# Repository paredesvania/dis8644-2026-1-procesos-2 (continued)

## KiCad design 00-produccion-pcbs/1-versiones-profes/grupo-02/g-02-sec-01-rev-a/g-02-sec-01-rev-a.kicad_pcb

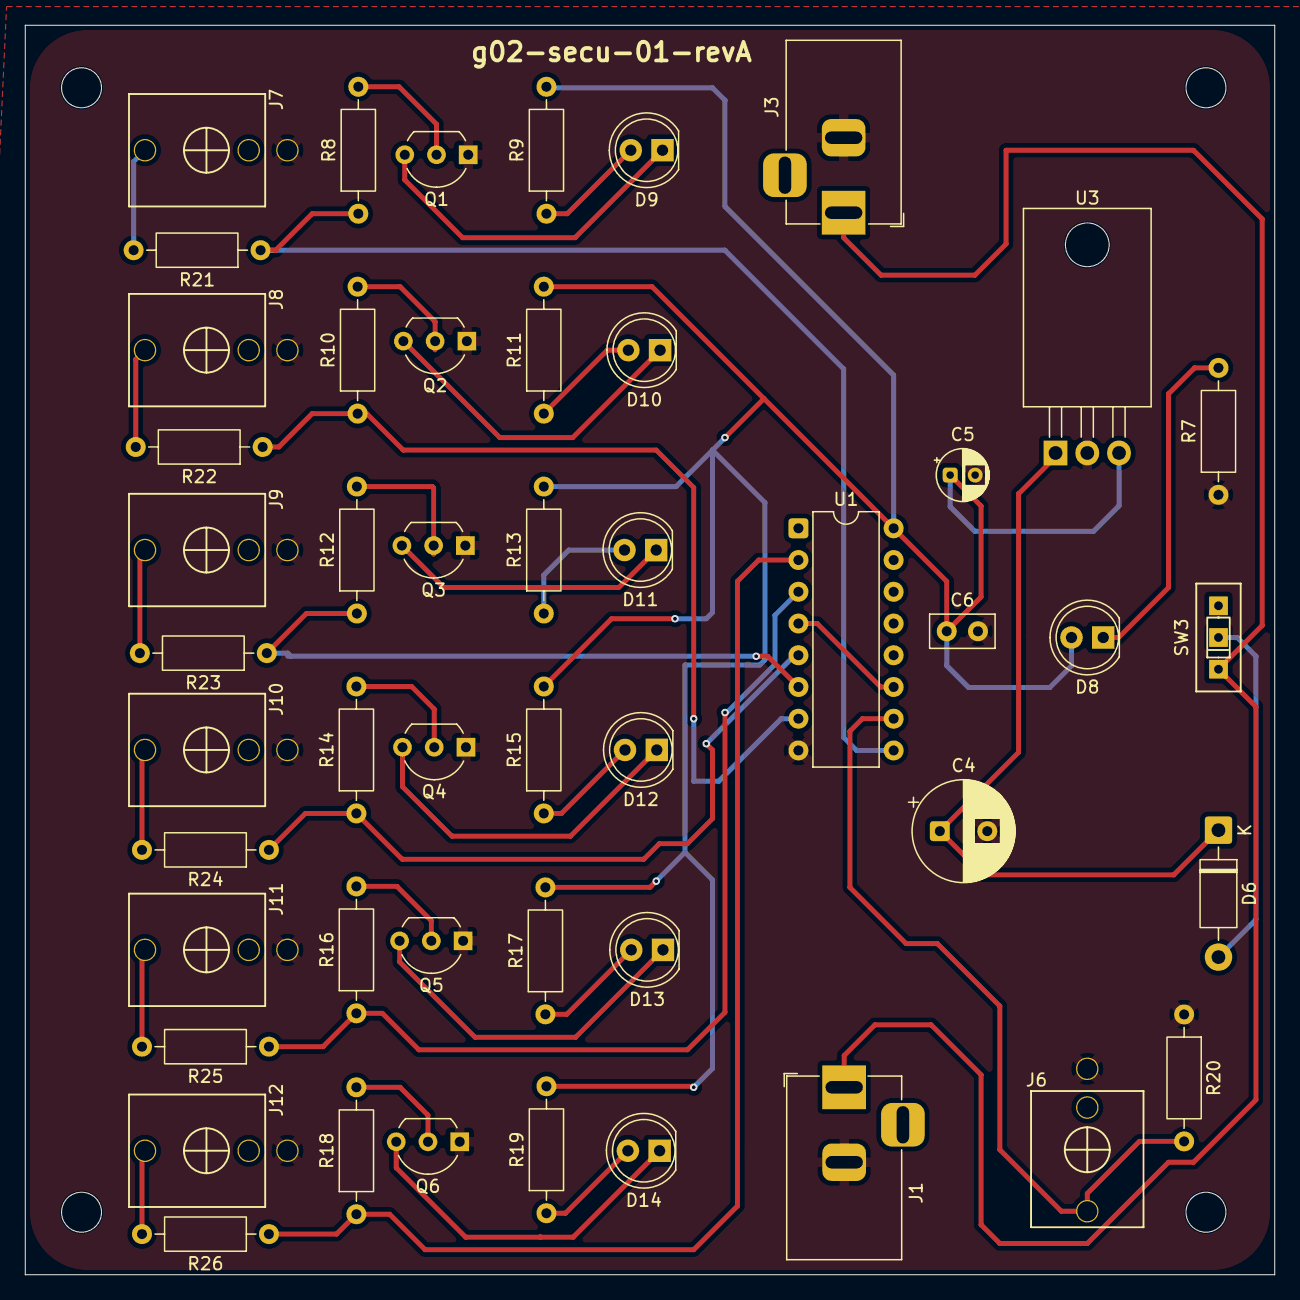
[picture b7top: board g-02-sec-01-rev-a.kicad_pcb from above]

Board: 2 copper layers, 100.0 x 100.0 mm, 53 parts (0 on the bottom side), 38 nets.

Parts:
C4: 100u; CP_Radial_D8.0mm_P3.80mm
C5: 10u; CP_Radial_D4.0mm_P2.00mm
C6: 100n; C_Disc_D5.0mm_W2.5mm_P2.50mm
D6: 1N4007; D_DO-41_SOD81_P10.16mm_Horizontal
D8, D9, D10, D11, D12, D13, D14: LED; LED_D5.0mm
H1, H2, H3, H4: M3; MountingHole_3.2mm_M3
J1, J3: Barrel_Jack_Switch; BarrelJack_Horizontal
J6, J7, J8, J9, J10, J11, J12: AudioJack2_SwitchT; PJ301M-12
Q1, Q2, Q3, Q4, Q5, Q6: PN2222A; TO-92_Inline_Wide
R7, R8, R9, R10, R11, R12, R13, R14, R15, R16, R17, R18, R19, R21, R22, R23, R24, R25, R26: 1k; R_Axial_DIN0207_L6.3mm_D2.5mm_P10.16mm_Horizontal
R20: 100k; R_Axial_DIN0207_L6.3mm_D2.5mm_P10.16mm_Horizontal
SW3: SW_SPDT; spdt_ssd12d00g3
U1: 4040; DIP-16_W7.62mm
U3: L7805; TO-220-3_Horizontal_TabDown

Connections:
+5V: C5.1, C6.1, D8.2 (A), R9.2, R11.2, R13.2, R15.2, R17.2, R19.2, U1.16 (VDD), U3.3 (OUT)
+12V: C4.1, D6.1 (K), U3.1 (IN)
GND: C4.2, C5.2, C6.2, J1.2, J3.2, J6.1, J7.1, J8.1, J9.1, J10.1, J11.1, J12.1, Q1.1 (E), Q2.1 (E), Q3.1 (E), Q4.1 (E), Q5.1 (E), Q6.1 (E), R7.1, R20.1, U1.8 (VSS), U3.2 (GND)
unnamed: D6.2 (A), SW3.2 (B)
unnamed: D8.1 (K), R7.2
unnamed: D9.2 (A), R9.1
unnamed: D9.1 (K), Q1.3 (C)
unnamed: D10.2 (A), R11.1
unnamed: D10.1 (K), Q2.3 (C)
unnamed: D11.2 (A), R13.1
unnamed: D11.1 (K), Q3.3 (C)
unnamed: D12.2 (A), R15.1
unnamed: D12.1 (K), Q4.3 (C)
unnamed: D13.2 (A), R17.1
unnamed: D13.1 (K), Q5.3 (C)
unnamed: D14.2 (A), R19.1
unnamed: D14.1 (K), Q6.3 (C)
unnamed: J7.3, R21.2
unnamed: J8.3, R22.2
unnamed: J9.3, R23.2
unnamed: J10.3, R24.2
unnamed: J11.3, R25.2
unnamed: J12.3, R26.2
unnamed: Q1.2 (B), R8.2
unnamed: Q2.2 (B), R10.2
unnamed: Q3.2 (B), R12.2
unnamed: Q4.2 (B), R14.2
unnamed: Q5.2 (B), R16.2
unnamed: Q6.2 (B), R18.2
unnamed: J1.1, J3.1, SW3.1 (A)
unnamed: J6.3, R20.2, U1.10 (CLK)
unnamed: R8.1, R21.1, U1.9 (Q0)
unnamed: R10.1, R22.1, U1.7 (Q1)
unnamed: R12.1, R23.1, U1.6 (Q2)
unnamed: R14.1, R24.1, U1.5 (Q3)
unnamed: R16.1, R25.1, U1.3 (Q4)
unnamed: R18.1, R26.1, U1.2 (Q5)
unnamed: U1.4 (Q6), U1.11 (Reset)

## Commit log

2026-05-15 imagenes-hola-todo-espero
2026-05-15 Update README.md by removing component table
    Removed component table and added a text reference to 'hacia una filosofia de la fotografia' by Vilem Flusser.
2026-05-15 agrego apuntes pencas para que no se me borre la info
2026-05-15 Rename imagen5.PNG to imagen5.png
2026-05-15 En edicion
    Added detailed descriptions of components and project information.
2026-05-19 no-cambio-tamano-voy-denuevo
2026-05-21 apuntes
    Added sections on class discussion and artist talk.
2026-05-21 fotikos
2026-05-21 avance-apunte-charla-y-jasper
2026-05-22 Expand README with analysis of photography philosophy
    Added analysis and reflection on chapters 4 and 5 of 'Filosofía de la Fotografía', discussing the impact of technology on creativity and perception.
2026-05-22 Add date to README for sesion-11b
2026-05-22 falta subir imagenes
    falta subir imagenes
2026-05-22 Enhance README with symbol and component usage instructions
    Added detailed instructions for modifying symbols, creating libraries, and using buttons and labels in the schematic. Included guidance on 3D modeling and exporting the complete board.
2026-05-22 sesion-in-correcta
2026-05-24 agrego apuntes charla
2026-05-24 apuntes
    Added a new section discussing Flusser's concepts of technical images and their implications on perception and photography.
2026-05-24 Add Flusser chapters to README
2026-05-25 avance-apunte-museo-sotc
2026-05-26 agrego v01 primera placa
2026-05-26 agrego v01 segunda placa
2026-05-26 Rename Captura de pantalla 2026-05-26 103945.png to esquematico01.png
2026-05-26 ignorar kicad history
2026-06-02 imagenes-piezo-musica
2026-06-02 Update README with class project details
    Added details about class activities and contributions.
2026-06-02 Revise README with circuit assembly updates
    Updated the README with details about circuit assembly and improvements made with the amplifier module.
2026-06-03 Create piezo-02-v03
2026-06-03 borrar a
2026-06-04 agrego switch
2026-06-04 agrego ayuda grupo
2026-06-04 agrego link
2026-06-04 eliminar archivo borrar
2026-06-04 agrego agradecimiento
2026-06-04 Create borrar
2026-06-05 agrego esquematico
2026-06-05 Rename esquematico-2 (1).png to esquematico-2.png
2026-06-05 traspaso apuntes trabajo en clase
2026-06-05 Fix image links and enhance collaboration section
    Updated image links and clarified circuit collaboration details.
2026-06-06 grupo-01 ok
2026-06-06 terminado g02
2026-06-06 corregido sec 02
2026-06-06 agregar zip
2026-06-06 cambiar zip
2026-06-06 añadido g-03-02
2026-06-12 Add session date and assignment details to README
2026-06-12 Rename Captura de pantalla 2026-06-12 112758.png to Conector-pogo.png
2026-06-15 Clase 9 de junio, falta agregar imagenes.md
2026-06-15 Revise README for project organization and filter details
    Updated the README.md to enhance project organization and clarify concepts related to the synthesizer and its filter functionality.
2026-06-15 EN EDICION
    Added additional images and updated the section on Yoko Ono's text.
2026-06-16 arreglo
2026-06-16 arreglo imagen lol
2026-06-16 Add images to README for visual reference
    Added images of 'partitura exterior' and 'partitura interior' to the README.
